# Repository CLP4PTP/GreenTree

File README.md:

Version 1.0: costs approx. 20 euros per tree, production work per tree approx. 3-4 hours
Used parts:
https://www.reichelt.de/my/1888149
Slide switch 3 positions: https://www.muekra.de/schiebeschalter.html
Feet (4x) https://www.horter-shop.de/de/self-adhesive-foot-m3/110-self-adhesive-foot-with-internal-thread-m3-4260404260011.html
9V batteries

For flashing, 150k resistors have turned out to be the best, as they flash at a pleasantly fast frequency.

Problems:
- Base board has already been changed to V2.0 (problem with transistor voltages have been fixed, but GND and VCC had to be swapped at the foot pins of the tree for this purpose) => LEDS must be soldered "wrong way around" on tree in version 1.0!
- Battery voltage drops from 9V to approx. 7V after a short period of operation. => Green, yellow and red LEDs go out very quickly because the voltage is too low
  Solution in V1.0: Bridge one LED per LED chain for green, yellow and red. Find a solution for this in the future or dimension the circuit correctly (e.g.buck converter to fixed voltage after battery)
- Extremely high soldering effort! Possible assembly e.g. from JLCPCB

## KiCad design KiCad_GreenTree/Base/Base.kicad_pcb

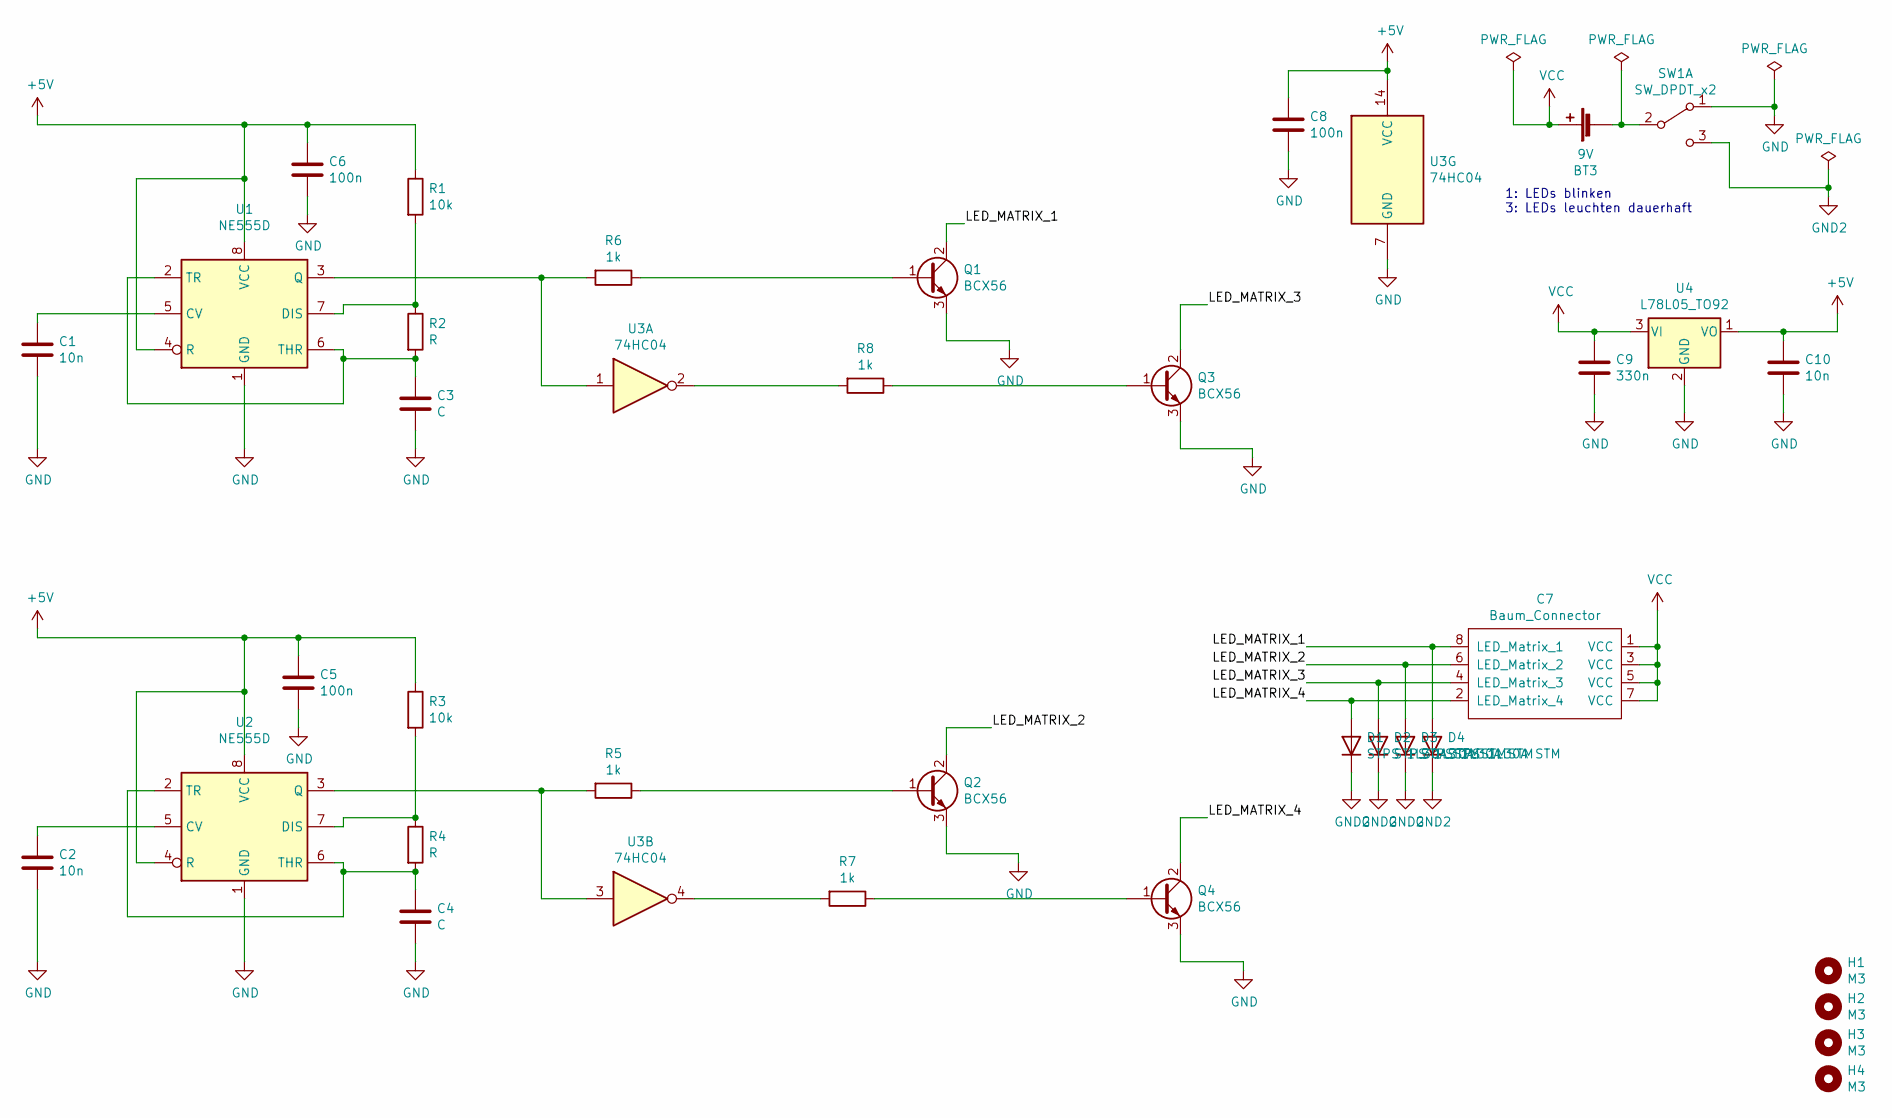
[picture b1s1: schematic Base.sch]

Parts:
BT3: 9V; 9V ohne Loecher
C1, C2, C10: 10n; C_0805_2012Metric_Pad1.18x1.45mm_HandSolder
C3, C4: C; C_0805_2012Metric_Pad1.18x1.45mm_HandSolder
C5, C6, C8: 100n; C_0805_2012Metric_Pad1.18x1.45mm_HandSolder
C7: Baum_Connector; Verbindung_Basis
C9: 330n; C_0805_2012Metric_Pad1.18x1.45mm_HandSolder
D1, D2, D3, D4: STPS 1L30A STM; D_SMA_Handsoldering
H1, H2, H3, H4: M3; MountingHole_3.2mm_M3
Q1, Q2, Q3, Q4: BCX56; SOT-89-3
R1, R3: 10k; R_0805_2012Metric_Pad1.20x1.40mm_HandSolder
R2, R4: R; R_0805_2012Metric_Pad1.20x1.40mm_HandSolder
R5, R6: 1k; R_1206_3216Metric_Pad1.30x1.75mm_HandSolder
R7, R8: 1k; R_0805_2012Metric_Pad1.20x1.40mm_HandSolder
SW1: SW_DPDT_x2; Schiebeschalter
U1, U2: NE555D; SOIC-8_3.9x4.9mm_P1.27mm
U3: 74HC04; SOIC-14_3.9x8.7mm_P1.27mm
U4: L78L05_TO92; TO-92_Inline

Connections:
+5V: C5.1, C6.1, C8.1, C10.1, R1.1, R3.1, U1.4 (R), U1.8 (VCC), U2.4 (R), U2.8 (VCC), U3.14 (VCC), U4.1 (VO)
/LED_MATRIX_1: C7.8 (LED_Matrix_1), D4.2 (A), Q1.2 (C)
/LED_MATRIX_2: C7.6 (LED_Matrix_2), D3.2 (A), Q2.2 (C)
/LED_MATRIX_3: C7.4 (LED_Matrix_3), D2.2 (A), Q3.2 (C)
/LED_MATRIX_4: C7.2 (LED_Matrix_4), D1.2 (A), Q4.2 (C)
GND: C1.2, C2.2, C3.2, C4.2, C5.2, C6.2, C8.2, C9.2, C10.2, Q1.3 (E), Q2.3 (E), Q3.3 (E), Q4.3 (E), SW1.1 (A), U1.1 (GND), U2.1 (GND), U3.7 (GND), U4.2 (GND)
GND2: D1.1 (K), D2.1 (K), D3.1 (K), D4.1 (K), SW1.3 (C)
unnamed: BT3.2 (-), SW1.2 (B)
unnamed: C1.1, U1.5 (CV)
unnamed: C2.1, U2.5 (CV)
unnamed: C3.1, R2.2, U1.2 (TR), U1.6 (THR)
unnamed: C4.1, R4.2, U2.2 (TR), U2.6 (THR)
unnamed: Q1.1 (B), R6.1
unnamed: Q2.1 (B), R5.1
unnamed: Q3.1 (B), R8.1
unnamed: Q4.1 (B), R7.1
unnamed: R1.2, R2.1, U1.7 (DIS)
unnamed: R3.2, R4.1, U2.7 (DIS)
unnamed: R5.2, U2.3 (Q), U3.3
unnamed: R6.2, U1.3 (Q), U3.1
unnamed: R7.2, U3.4
unnamed: R8.2, U3.2
VCC: BT3.1 (+), C7.1 (VCC), C7.3 (VCC), C7.5 (VCC), C7.7 (VCC), C9.1, U4.3 (VI)

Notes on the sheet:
1: LEDs blinken 3: LEDs leuchten dauerhaft

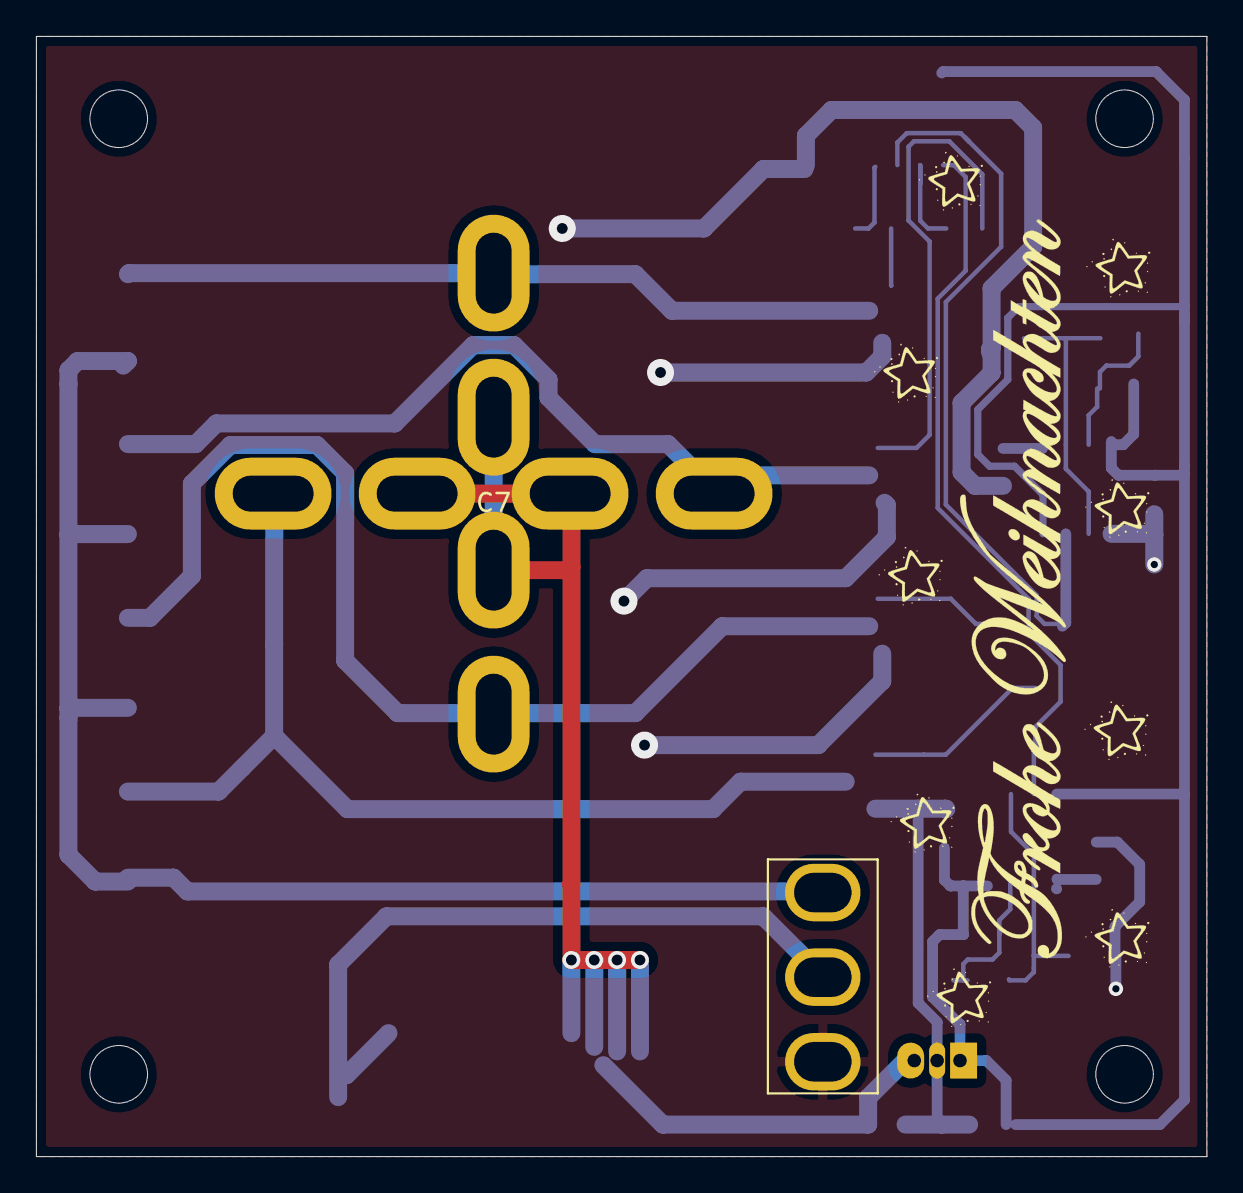
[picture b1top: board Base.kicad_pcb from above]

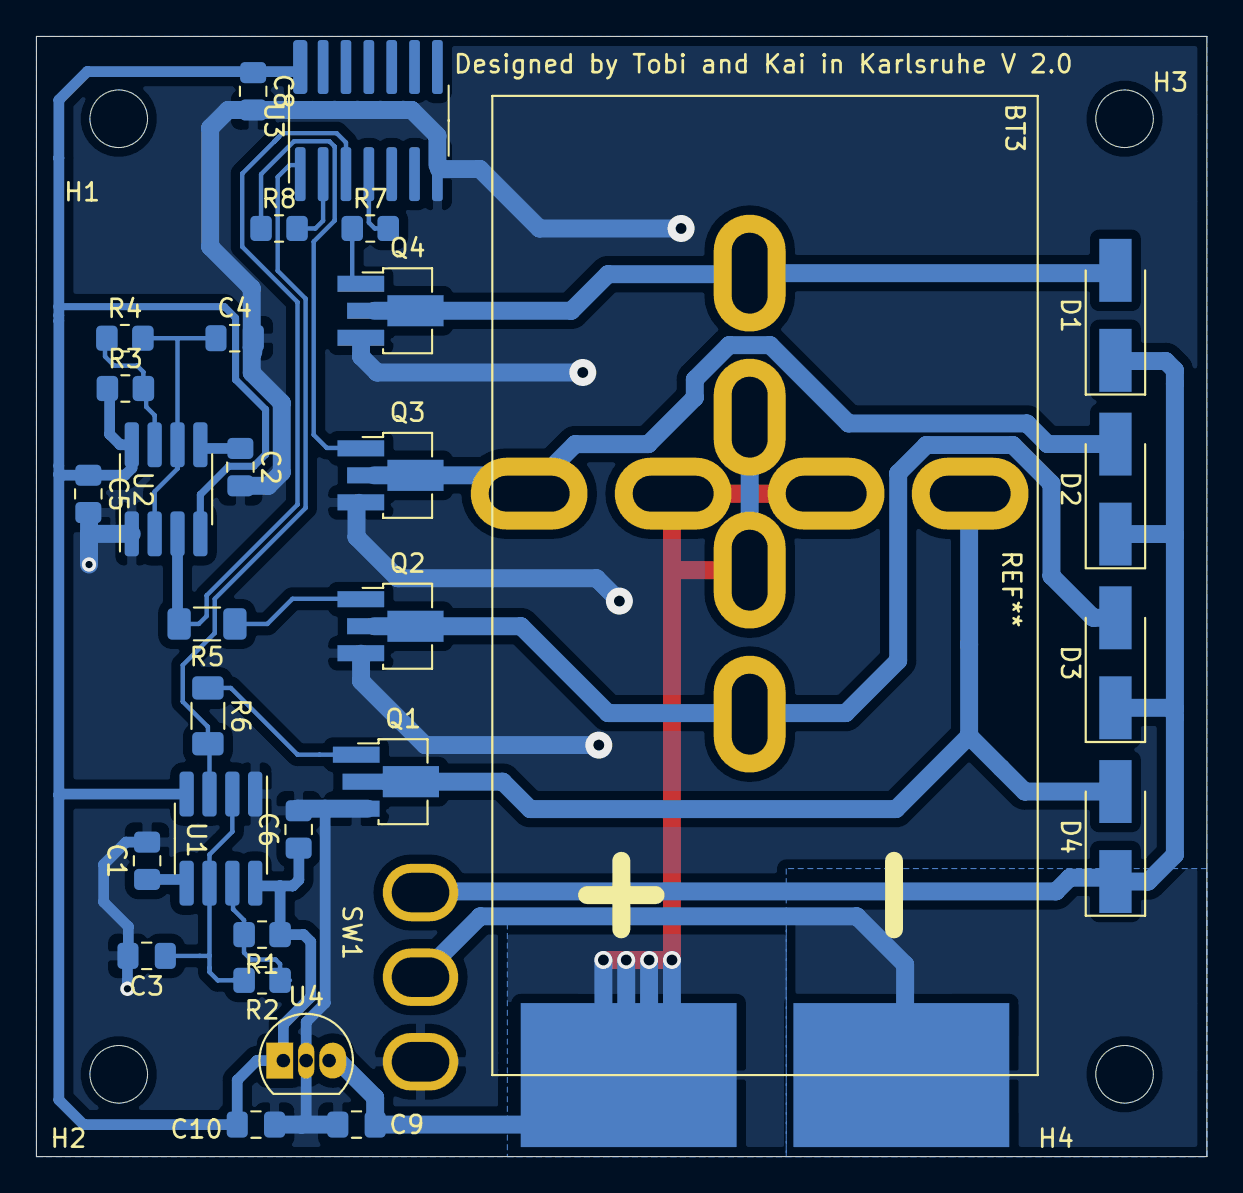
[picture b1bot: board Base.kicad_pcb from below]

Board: 2 copper layers, 65.0 x 62.2 mm, 36 parts (30 on the bottom side), 23 nets.

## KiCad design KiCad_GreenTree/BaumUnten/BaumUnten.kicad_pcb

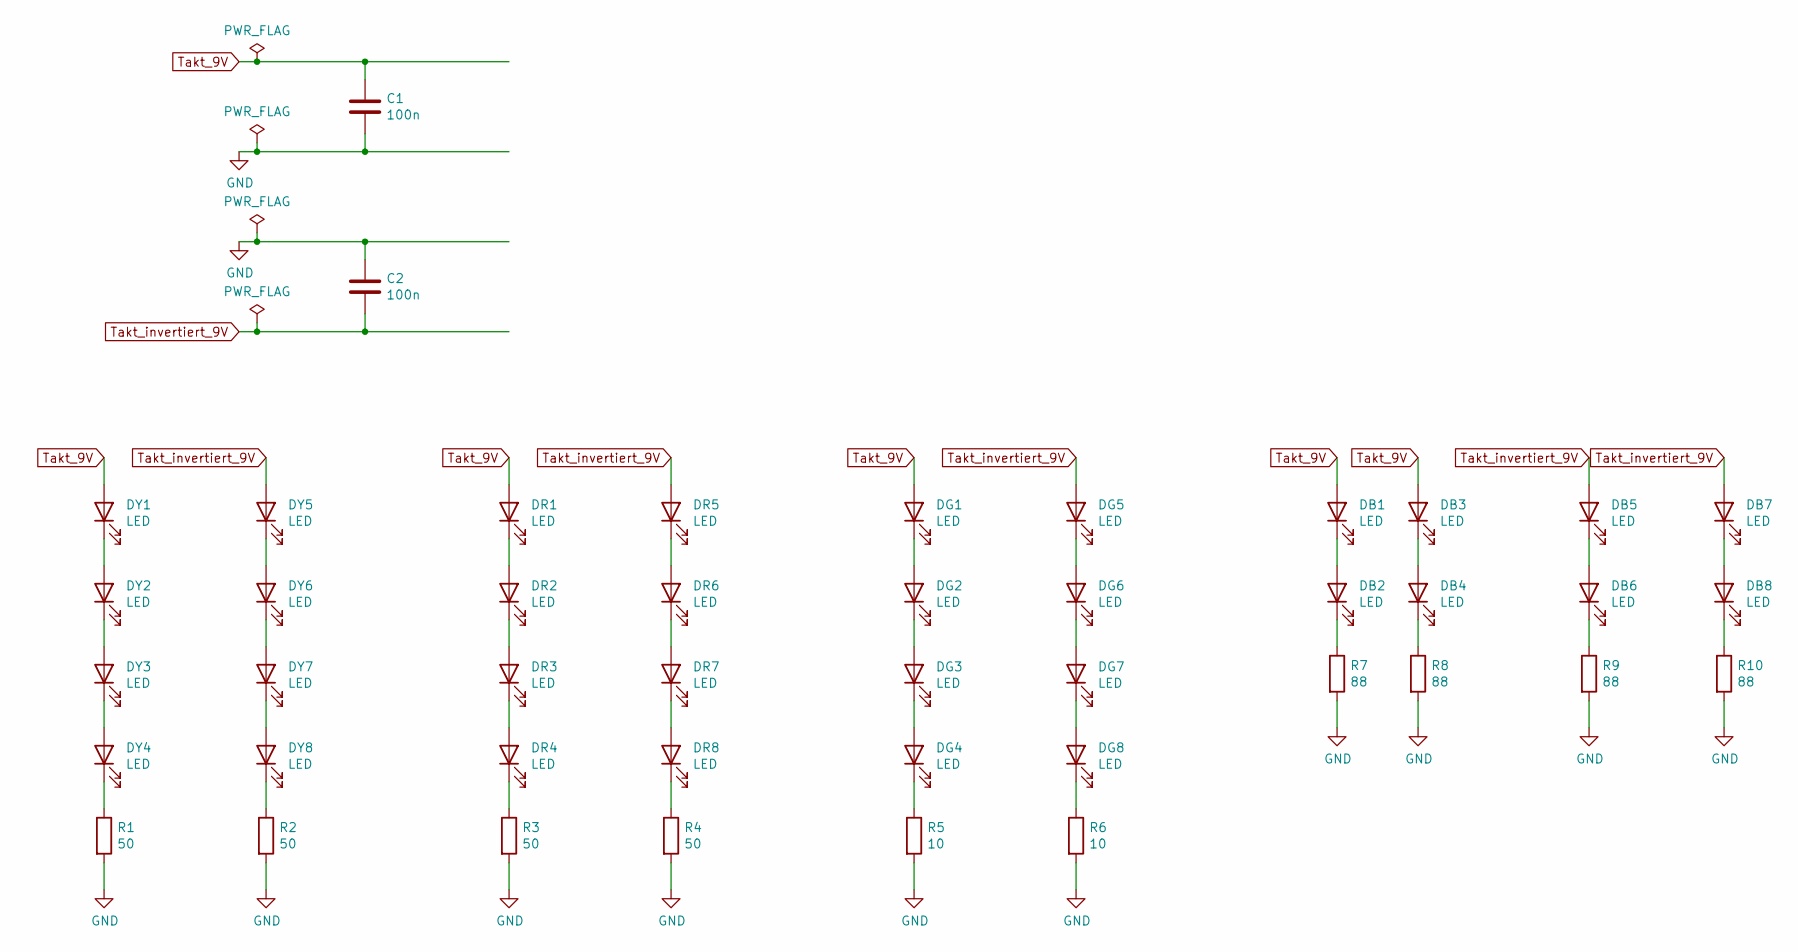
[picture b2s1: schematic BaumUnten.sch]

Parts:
C1, C2: 100n; C_0805_2012Metric_Pad1.15x1.40mm_HandSolder
DB1, DB2, DB3, DB4, DB5, DB6, DB7, DB8: LED; D_0603_1608Metric_Pad1.05x0.95mm_HandSolder
DG1, DG2, DG3, DG4, DG5, DG6, DG7, DG8: LED; D_0805_2012Metric_Pad1.15x1.40mm_HandSolder
DR1, DR2, DR3, DR4, DR5, DR6, DR7, DR8: LED; D_0805_2012Metric_Pad1.15x1.40mm_HandSolder
DY1, DY2, DY3, DY4, DY5, DY6, DY7, DY8: LED; D_0805_2012Metric_Pad1.15x1.40mm_HandSolder
R1, R2, R3, R4: 50; R_0805_2012Metric_Pad1.15x1.40mm_HandSolder
R5, R6: 10; R_0805_2012Metric_Pad1.15x1.40mm_HandSolder
R7, R8, R9, R10: 88; R_0805_2012Metric_Pad1.15x1.40mm_HandSolder

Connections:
GND: C1.2, C2.1, R1.2, R2.2, R3.2, R4.2, R5.2, R6.2, R7.2, R8.2, R9.2, R10.2
unnamed: DB1.1 (K), DB2.2 (A)
unnamed: DB2.1 (K), R7.1
unnamed: DB3.1 (K), DB4.2 (A)
unnamed: DB4.1 (K), R8.1
unnamed: DB5.1 (K), DB6.2 (A)
unnamed: DB6.1 (K), R9.1
unnamed: DB7.1 (K), DB8.2 (A)
unnamed: DB8.1 (K), R10.1
unnamed: DG1.1 (K), DG2.2 (A)
unnamed: DG2.1 (K), DG3.2 (A)
unnamed: DG3.1 (K), DG4.2 (A)
unnamed: DG4.1 (K), R5.1
unnamed: DG5.1 (K), DG6.2 (A)
unnamed: DG6.1 (K), DG7.2 (A)
unnamed: DG7.1 (K), DG8.2 (A)
unnamed: DG8.1 (K), R6.1
unnamed: DR1.1 (K), DR2.2 (A)
unnamed: DR2.1 (K), DR3.2 (A)
unnamed: DR3.1 (K), DR4.2 (A)
unnamed: DR4.1 (K), R3.1
unnamed: DR5.1 (K), DR6.2 (A)
unnamed: DR6.1 (K), DR7.2 (A)
unnamed: DR7.1 (K), DR8.2 (A)
unnamed: DR8.1 (K), R4.1
unnamed: DY1.1 (K), DY2.2 (A)
unnamed: DY2.1 (K), DY3.2 (A)
unnamed: DY3.1 (K), DY4.2 (A)
unnamed: DY4.1 (K), R1.1
unnamed: DY5.1 (K), DY6.2 (A)
unnamed: DY6.1 (K), DY7.2 (A)
unnamed: DY7.1 (K), DY8.2 (A)
unnamed: DY8.1 (K), R2.1
Takt_9V: C1.1, DB1.2 (A), DB3.2 (A), DG1.2 (A), DR1.2 (A), DY1.2 (A)
Takt_invertiert_9V: C2.2, DB5.2 (A), DB7.2 (A), DG5.2 (A), DR5.2 (A), DY5.2 (A)

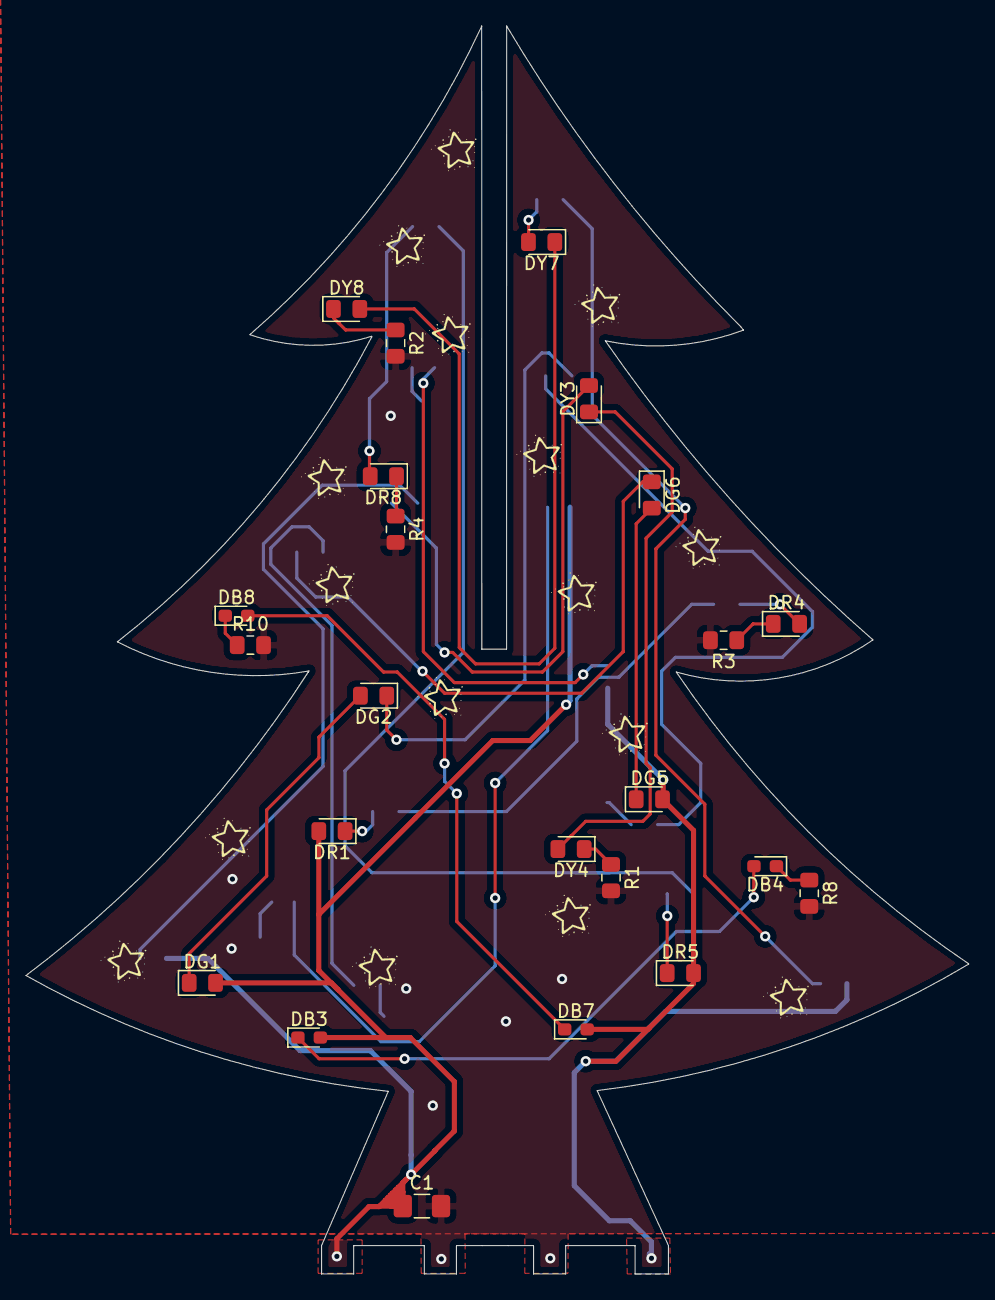
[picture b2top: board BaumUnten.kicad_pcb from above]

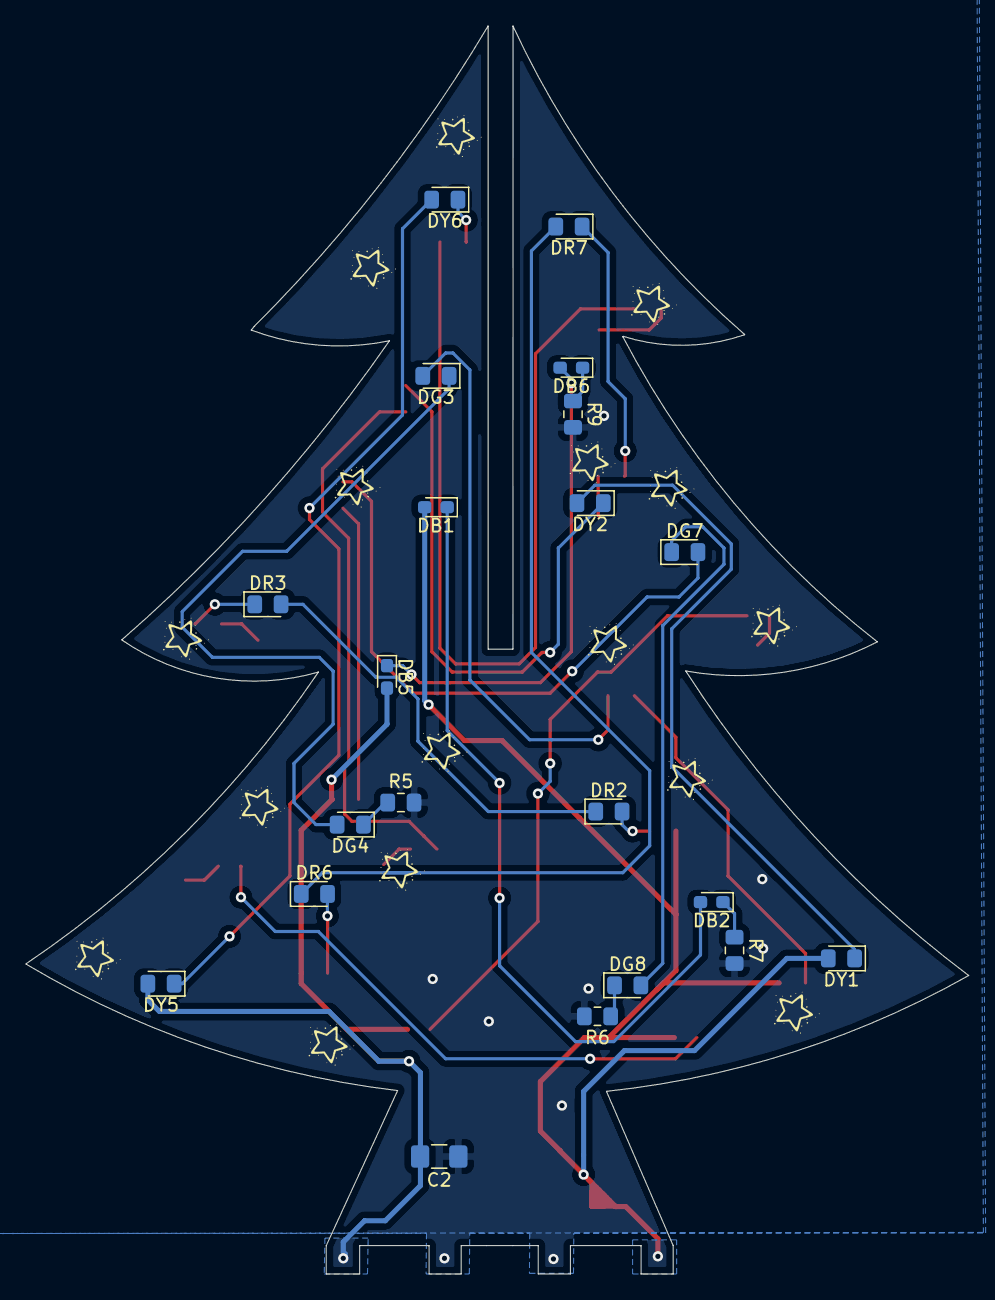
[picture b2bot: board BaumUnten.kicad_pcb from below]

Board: 2 copper layers, 73.4 x 97.1 mm, 44 parts (21 on the bottom side), 35 nets.

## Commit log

2021-10-15 init Kicad
2021-10-15 KiCadInit
2021-10-16 Batteriehalter
2021-10-16 Update Reichelt-Bauteile
2021-10-17 Baum oben pcb outline fertig
2021-10-17 some work on Base
2021-10-17 Verbindung zu Baum
2021-10-17 NE555 Layout
2021-10-18 Update fp-info-cache
2021-10-18 Without GND
2021-10-18 Entwurf1
2021-10-18 Schaltplan oben
    Schaltplan oben fertig und Layout angefangen
2021-10-19 layout weiter gemacht
2021-10-19 gerber kaputt
2021-10-19 fixed Edge Cuts
2021-10-19 BaumOben fertig
2021-10-19 baum unten sachen kopiert
2021-10-20 ordentlicher Schaltplan
    NO DRC errors anymore
2021-10-20 Added Diodes
2021-10-20 fixed Diodes
2021-10-20 added 5V
2021-10-20 fixed Inv
2021-10-20 bis auf silk fertig
    baum unten fertig gemacht und Beinchen gekürzt
2021-10-23 sterne auf silkscreen baum
2021-10-24 Schlitz korrigiert und Schrift Base
2021-10-24 update Bauteilliste
2021-10-25 optimierung der Leitungen
2021-10-27 edgecuts angepasst
2021-10-27 final
2021-10-27 footprint auf 0805
2021-11-03 Bohrdatein
2021-11-16 nothing works
    Transistoren gegen GND schalten
    Footprint Inverter und Schalter ändern
    Inverter Spannungslevel anpassen. (Schalten der Transistoren beachten)
    SMD linearregler?
    Größere Widerstande bestellen
    Andere Füße
2021-11-17 Base V2.0
    Finished Rework. Sould now work. Hoping for the best
2021-11-18 V 2.0
2021-11-19 Order JLCPCB
2021-11-19 Replacmentfile JLC
    fixed bug where outline of Switch was Sodermask insted of silkscreen
